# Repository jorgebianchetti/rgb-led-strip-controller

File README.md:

# rgb-led-strip-controller
A non-addressable RGB LED strip controller for Texas Instruments CC2640R2F

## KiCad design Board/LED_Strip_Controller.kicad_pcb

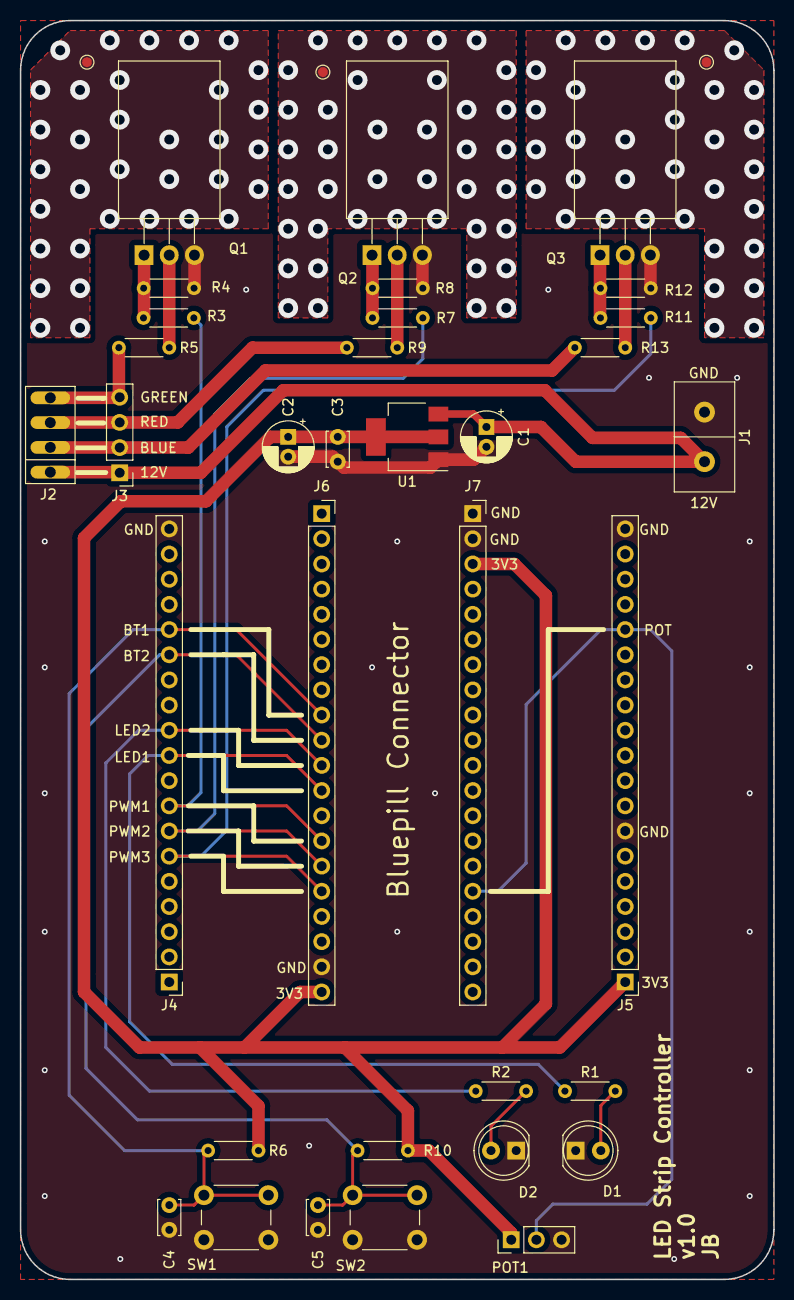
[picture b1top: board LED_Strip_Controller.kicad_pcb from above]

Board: 2 copper layers, 76.0 x 127.0 mm, 37 parts (0 on the bottom side), 23 nets.

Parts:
C1, C2: CP; CP_Radial_D5.0mm_P2.00mm
C3, C4, C5: C; C_Disc_D3.4mm_W2.1mm_P2.50mm
D1, D2: LED; LED_D5.0mm
H1, H2, H3: MountingHole_Pad; TestPoint_Pad_D1.0mm
J1: Conn_01x02_Male; SIP-2
J2: Conn_01x04_Male; SIP-4
J3: Conn_01x04_Male; PinHeader_1x04_P2.54mm_Vertical
J4, J5: Conn_01x19_Male; PinHeader_1x19_P2.54mm_Vertical
J6, J7: Conn_01x20_Male; PinSocket_1x20_P2.54mm_Vertical
POT1: R_POT; PinHeader_1x03_P2.54mm_Vertical
Q1, Q2, Q3: TIP41A; TO-220-3_Horizontal_TabDown
R1, R2, R3, R4, R5, R6, R7, R8, R9, R10, R11, R12, R13: R; R_Axial_DIN0204_L3.6mm_D1.6mm_P5.08mm_Horizontal
SW1, SW2: SW_Push_Dual; SW_PUSH_6mm_H7.3mm
U1: LM1117-3.3; SOT-223-3_TabPin2

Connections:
+3V3: C2.1, C3.1, J5.1, J6.20, J7.3, POT1.1, R6.1, R10.1, U1.2
+12V: C1.1, J1.1, J2.1, J3.1, U1.3
/ADC1: J5.15, J7.16, POT1.2
/BT1: C4.1, J4.15, J6.9, R6.2, SW1.2
/BT2: C5.1, J4.14, J6.10, R10.2, SW2.2
/LED1: J4.10, J6.12, R1.1
/LED2: J4.11, J6.11, R2.1
/LED_B: J2.2, J3.2, R13.1
/LED_G: J2.4, J3.4, R5.1
/LED_R: J2.3, J3.3, R9.1
/PWM1: J4.8, J6.14, R3.2
/PWM2: J4.7, J6.15, R7.2
/PWM3: J4.6, J6.16, R11.2
/thermal: H1.1, H2.1, H3.1
GND: C1.2, C2.2, C3.2, C4.2, C5.2, D1.1, D2.1, J1.2, J4.19, J5.7, J5.19, J6.19, J7.1, J7.2, POT1.3, Q1.3, Q2.3, Q3.3, R4.1, R8.1, R12.1, SW1.1, SW2.1, U1.1
unnamed: D1.2, R1.2
unnamed: D2.2, R2.2
unnamed: Q1.1, R3.1, R4.2
unnamed: Q1.2, R5.2
unnamed: Q2.1, R7.1, R8.2
unnamed: Q2.2, R9.2
unnamed: Q3.1, R11.1, R12.2
unnamed: Q3.2, R13.2

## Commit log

2020-10-25 Add files
2020-10-29 Add BLE config support
